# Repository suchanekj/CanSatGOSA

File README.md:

# About
CanSat code is software for autonomous exploration and landings of probe "CanSat" developed by Gymnazium Opatov Space Agency especially by Jakub Suchánek.

The whole code is using following subcodes:
* GroundStation - incoming datas of pressure, position, time and temperature
* Cansat (2.0) - used libraries - Code, Cirtuits...
* Final report (Detail information about the probe Cansat in LaTex article. Unfortunately only in Czech.)
* Pre launch report - English detail description of Cansat 2.0
* Analysis - our own atmospheric model running on data from CanSat
* After flight report - final description of the whole project

# Support
In case you need help with use of our program or support us, you can contact us on our public email dotazy@gosa.cz or on email of programming director suchanek989@seznam.cz

# Contributing

Contributions are welcome and encouraged.  You can contribute in many ways:

* Documentation updates and corrections.
* How-To guides - received help? Help others!
* Bug reporting & fixes.
* New feature ideas & suggestions.

# Requirements
* Hardware requirements: qbcan for matching ports or an AVR microcontroller with RFM69HW (will have to edit port specifications)
* Idealy used for original construction of CanSat: https://github.com/suchanekj/CanSatGOSA/tree/master/Schematics
* Also used for original construction of CanSat 2.0: https://github.com/suchanekj/CanSatGOSA/tree/master/CanSat2.0/Schematics 
* Software requirements: AVR chip programmmer

# Used code
* Uses the RFM69 Library from: Feix Rusu (2014), felix@lowpowerlab.com http://lowpowerlab.com/
* Inspired by qbcan library and hardware http://doc.open-cosmos.com/Qbcan_modular

# Open Source / Contributors
CanSat software that is **open source** and is available free of charge without warranty to all users.

Current contributors:
* Suchánek, Jakub (suchanekj)
* Novotný, Patrik  (PatriktheAstronomer)
* Vítek, Martin (MArtytraM99)
* Zeman, Jakub (Jakubzmn)
* Völfl, Lukáš (LukasVolfl)
# Versions:
* 1.0 Groundstation subcode created and README added 29/03/2018
* 1.1 CanSat subcode created and Model files completed 01/04/2018
* 1.2 Final report (LaTex article) created 03/04/2018
* 1.3 Final report (LaTex article) completed 12/04/2018
* 2.0 New contributers, Analysis, CanSat 2.0 3D printed parts and PLR.pdf (Pre-launch report) added 18/06/2018
* 2.1 Analysis part 2 completed, chamber software added 28/06/2018
* 2.2 After flight report added, Analysis repaired and added - project completely done 16/07/2018
 (**Thanks everyone for your support to our project!**)

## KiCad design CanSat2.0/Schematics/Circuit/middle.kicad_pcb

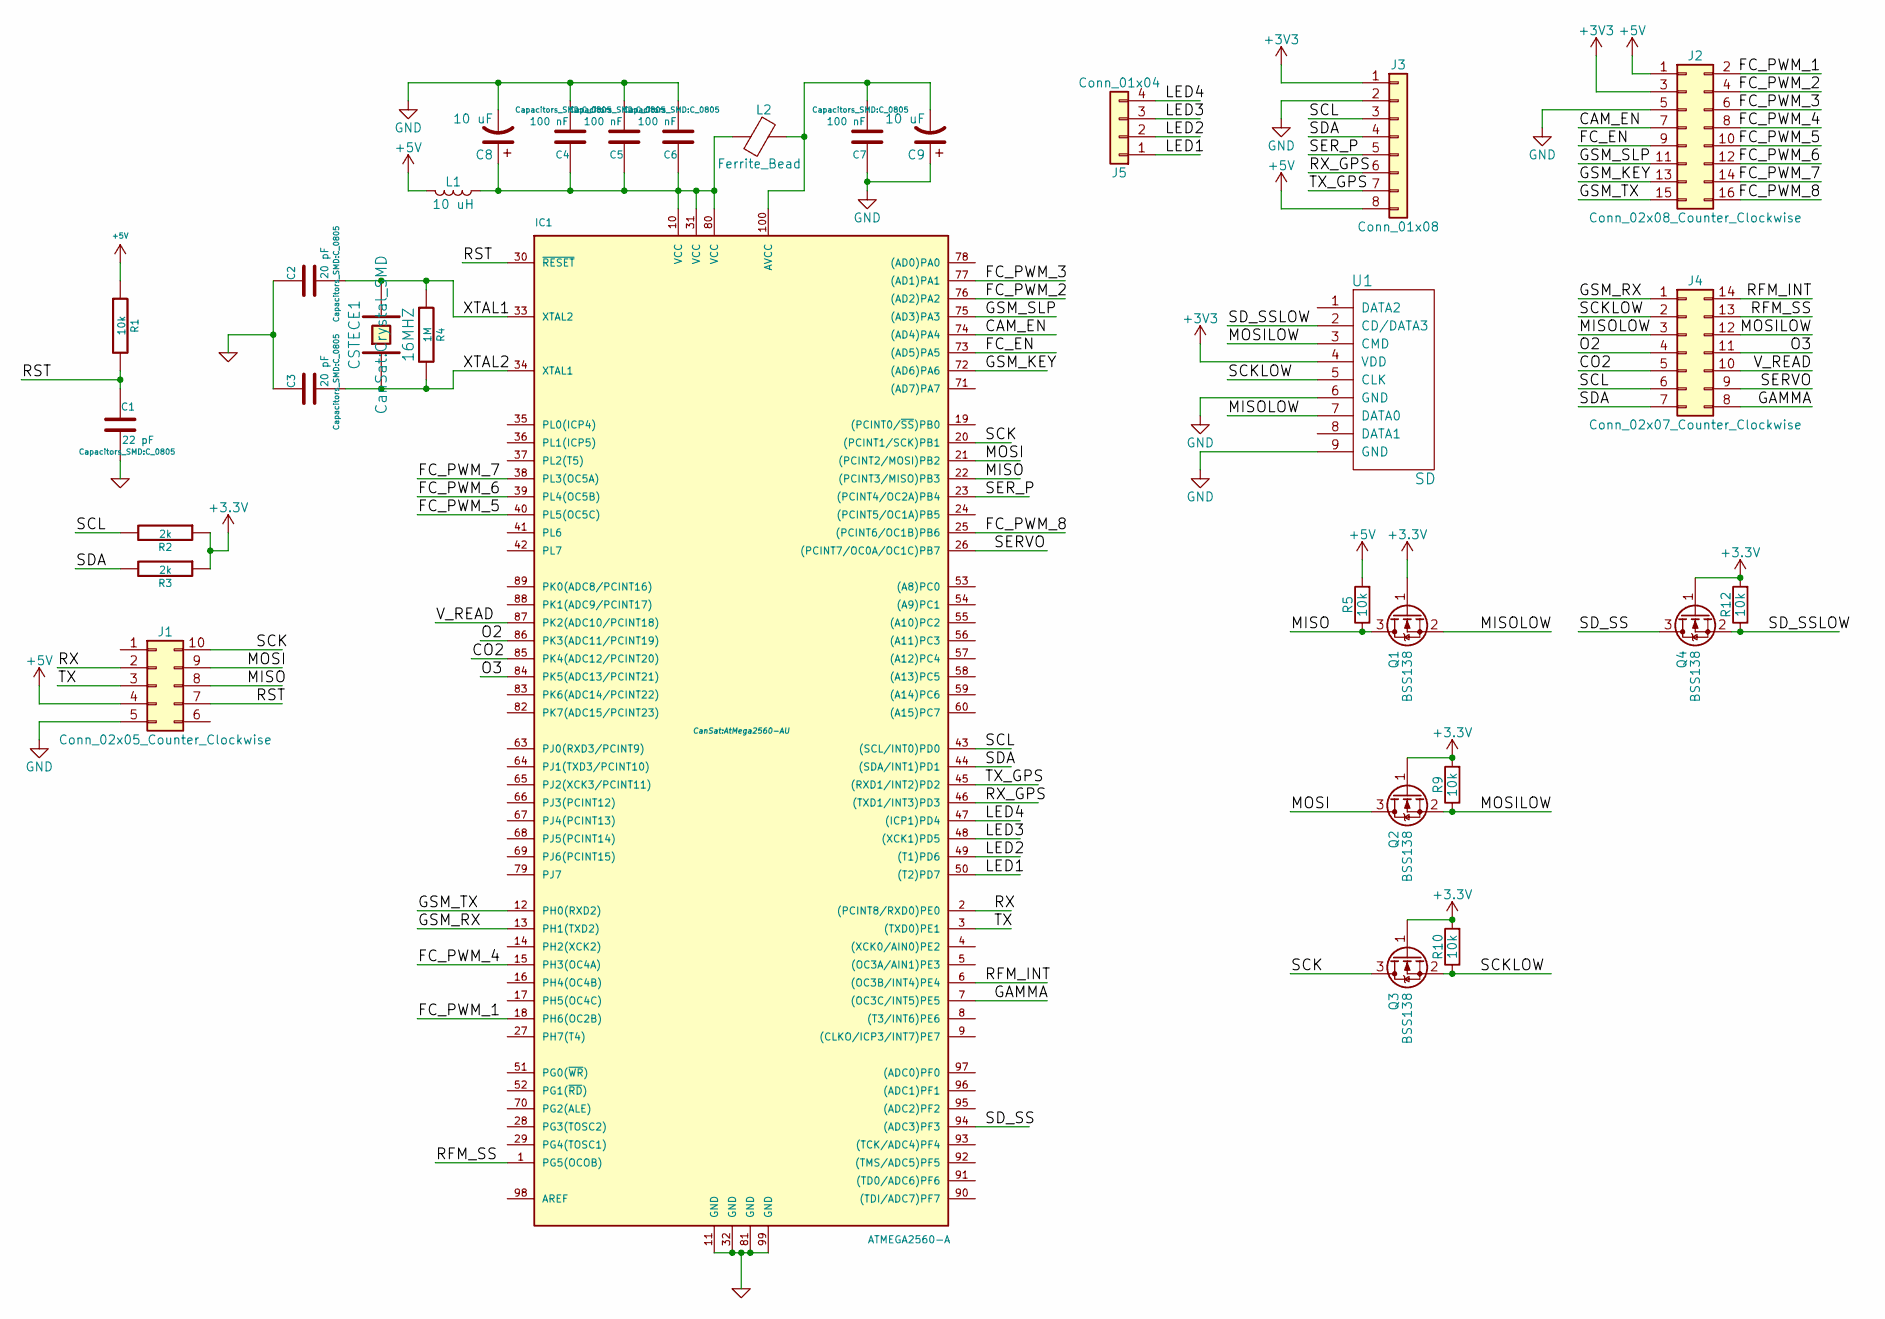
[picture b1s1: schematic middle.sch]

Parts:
C1: 22 pF; C_0805
C2, C3: 20 pF; C_0805
C4, C5, C6, C7: 100 nF; C_0805
C8, C9: 10 uF; CP_Tantalum_Case-B_EIA-3528-21_Reflow
CSTECE1: 16MHZ; Crystal_SMD
IC1: ATMEGA2560-A; AtMega2560-AU
J1: Conn_02x05_Counter_Clockwise; Pin_Header_Straight_2x05_Pitch1.27mm
J2: Conn_02x08_Counter_Clockwise; Pin_Header_Straight_2x08_Pitch1.27mm
J3: Conn_01x08; Pin_Header_Straight_1x08_Pitch1.27mm
J4: Conn_02x07_Counter_Clockwise; Pin_Header_Straight_2x07_Pitch1.27mm
J5: Conn_01x04; Pin_Header_Straight_1x04_Pitch1.27mm
L1: 10 uH; L_Taiyo-Yuden_NR-50xx
L2: Ferrite_Bead; L_0805
Q1, Q2, Q3, Q4: BSS138; SOT-23
R1, R5, R9, R10, R12: 10k; R_0805
R2, R3: 2k; R_0805
R4: 1M; R_0805
U1: SD

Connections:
+5V: J1.4, J2.1, J3.8, L1.2, R1.1, R5.2
/CAM_EN: IC1.74 ((AD4)PA4), J2.7
/CO2: IC1.85 (PK4(ADC12/PCINT20)), J4.5
/FC_EN: IC1.73 ((AD5)PA5), J2.9
/FC_PWM_1: IC1.18 (PH6(OC2B)), J2.2
/FC_PWM_2: IC1.76 ((AD2)PA2), J2.4
/FC_PWM_3: IC1.77 ((AD1)PA1), J2.6
/FC_PWM_4: IC1.15 (PH3(OC4A)), J2.8
/FC_PWM_5: IC1.40 (PL5(OC5C)), J2.10
/FC_PWM_6: IC1.39 (PL4(OC5B)), J2.12
/FC_PWM_7: IC1.38 (PL3(OC5A)), J2.14
/FC_PWM_8: IC1.25 ((PCINT6/OC1B)PB6), J2.16
/GAMMA: IC1.7 ((OC3C/INT5)PE5), J4.8
/GSM_KEY: IC1.72 ((AD6)PA6), J2.13
/GSM_RX: IC1.13 (PH1(TXD2)), J4.1
/GSM_SLP: IC1.75 ((AD3)PA3), J2.11
/GSM_TX: IC1.12 (PH0(RXD2)), J2.15
/LED1: IC1.50 ((T2)PD7), J5.1
/LED2: IC1.49 ((T1)PD6), J5.2
/LED3: IC1.48 ((XCK1)PD5), J5.3
/LED4: IC1.47 ((ICP1)PD4), J5.4
/MISO: IC1.22 ((PCINT3/MISO)PB3), J1.8, Q1.3 (D), R5.1
/MISOLOW: J4.3, Q1.2 (S), U1.7 (DATA0)
/MOSI: IC1.21 ((PCINT2/MOSI)PB2), J1.9, Q2.3 (D)
/MOSILOW: J4.12, Q2.2 (S), R9.1, U1.3 (CMD)
/O2: IC1.86 (PK3(ADC11/PCINT19)), J4.4
/O3: IC1.84 (PK5(ADC13/PCINT21)), J4.11
/RFM_INT: IC1.6 ((OC3B/INT4)PE4), J4.14
/RFM_SS: IC1.1 (PG5(OCOB)), J4.13
/RST: C1.1, IC1.30 (~RESET), J1.7, R1.2
/RX: IC1.2 ((PCINT8/RXD0)PE0), J1.2
/RX_GPS: IC1.46 ((TXD1/INT3)PD3), J3.6
/SCK: IC1.20 ((PCINT1/SCK)PB1), J1.10, Q3.3 (D)
/SCKLOW: J4.2, Q3.2 (S), R10.1, U1.5 (CLK)
/SCL: IC1.43 ((SCL/INT0)PD0), J3.3, J4.6, R2.2
/SDA: IC1.44 ((SDA/INT1)PD1), J3.4, J4.7, R3.2
/SD_SS: IC1.94 ((ADC3)PF3), Q4.3 (D)
/SD_SSLOW: Q4.2 (S), R12.1, U1.2 (CD/DATA3)
/SERVO: IC1.26 ((PCINT7/OC0A/OC1C)PB7), J4.9
/SER_P: IC1.23 ((PCINT4/OC2A)PB4), J3.5
/TX: IC1.3 ((TXD0)PE1), J1.3
/TX_GPS: IC1.45 ((RXD1/INT2)PD2), J3.7
/V_READ: IC1.87 (PK2(ADC10/PCINT18)), J4.10
/XTAL1: C2.2, CSTECE1.2, IC1.33 (XTAL2), R4.1
/XTAL2: C3.2, CSTECE1.1, IC1.34 (XTAL1), R4.2
GND: C1.2, C2.1, C3.1, C4.2, C5.2, C6.2, C7.1, C8.2, C9.1, IC1.11 (GND), IC1.32 (GND), IC1.81 (GND), IC1.99 (GND), J1.5, J2.5, J3.2, U1.6 (GND), U1.9 (GND)
unnamed: C4.1, C5.1, C6.1, C8.1, IC1.10 (VCC), IC1.31 (VCC), IC1.80 (VCC), L1.1, L2.2
unnamed: C7.2, C9.2, IC1.100 (AVCC), L2.1

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
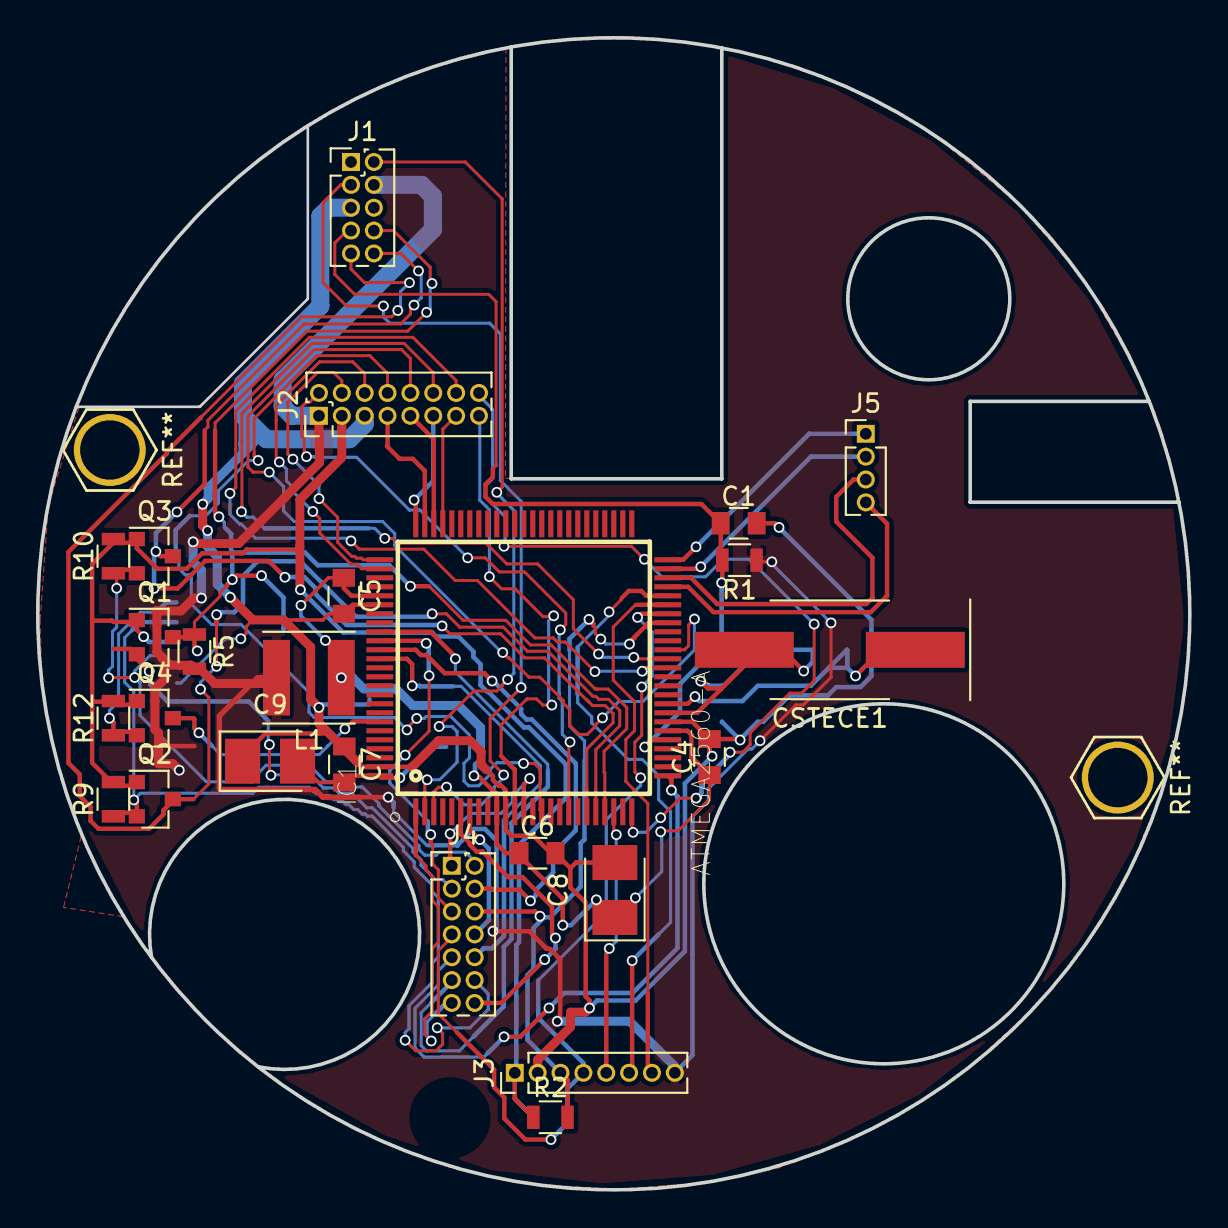
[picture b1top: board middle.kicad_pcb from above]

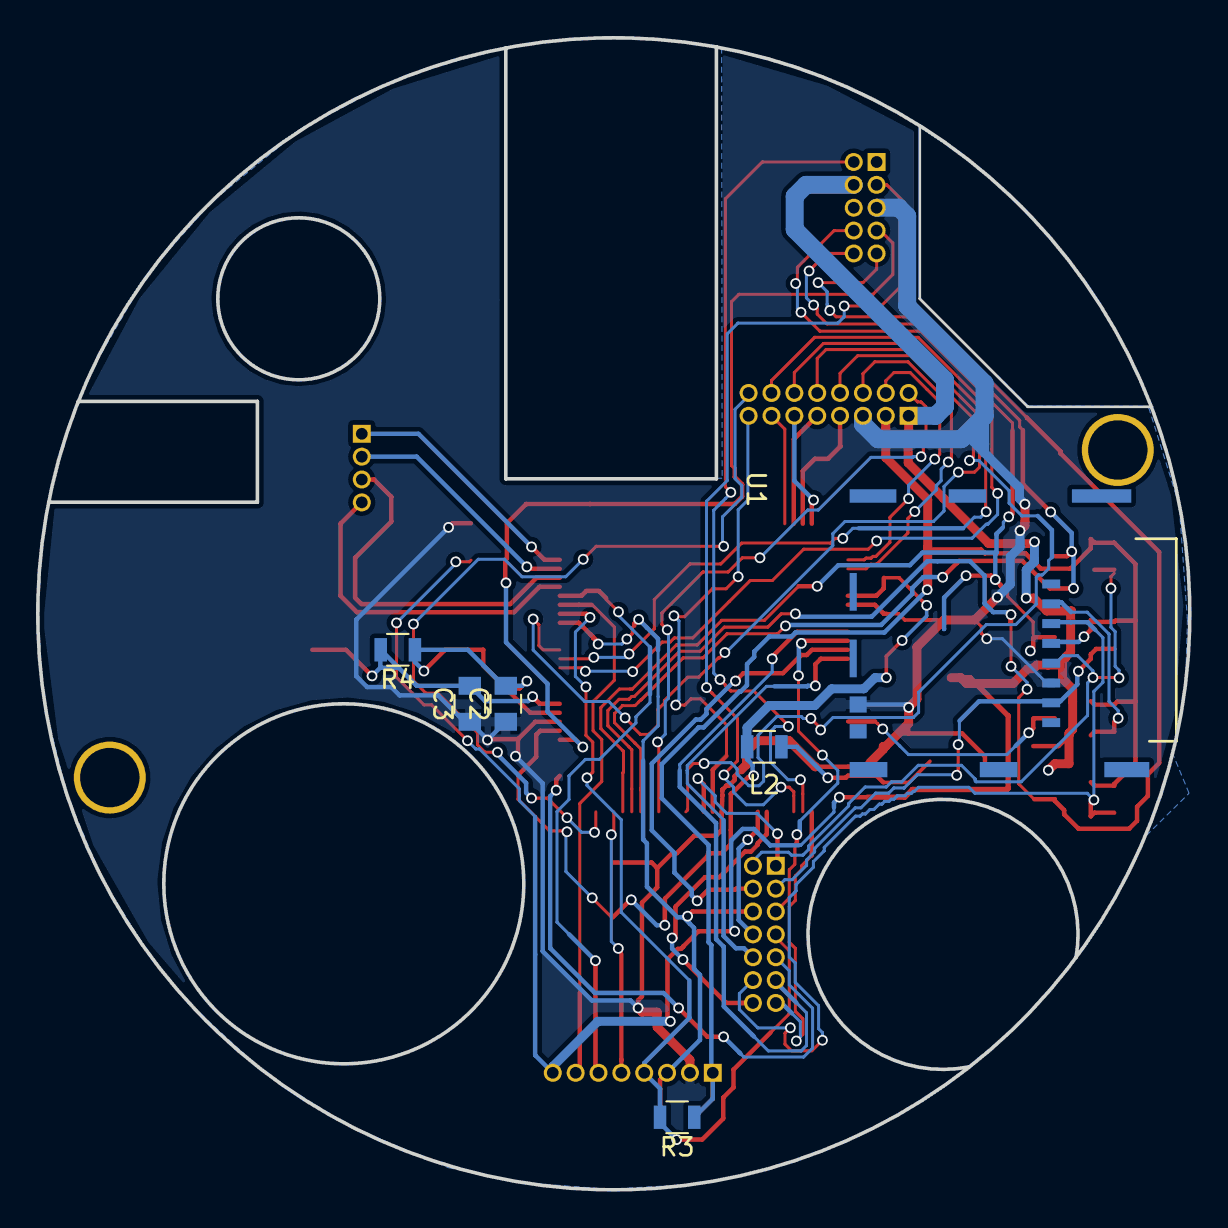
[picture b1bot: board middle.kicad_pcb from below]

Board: 2 copper layers, 64.0 x 64.0 mm, 31 parts (6 on the bottom side), 49 nets.

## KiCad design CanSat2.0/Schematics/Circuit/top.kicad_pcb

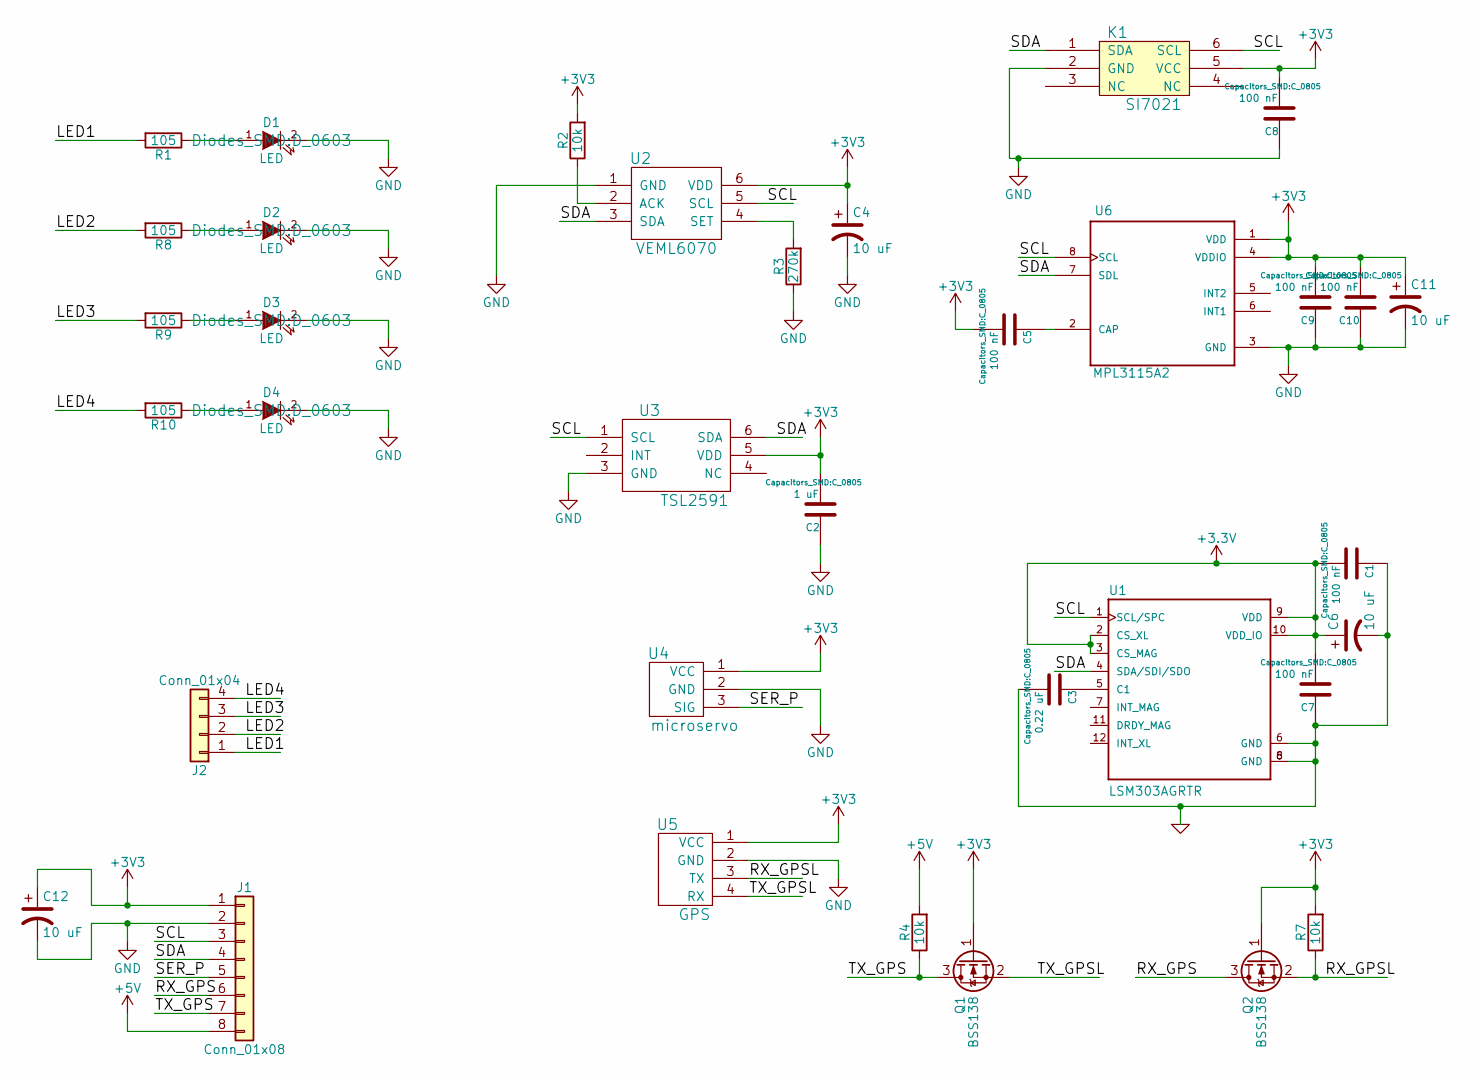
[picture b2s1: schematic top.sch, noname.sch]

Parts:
C1, C5, C7, C8, C9, C10: 100 nF; C_0805
C2: 1 uF; C_0805
C3: 0.22 uF; C_0805
C4, C6, C11, C12: 10 uF; CP_Tantalum_Case-T_EIA-3528-12_Reflow
D1, D2, D3, D4: LED; D_0603
J1: Conn_01x08; Pin_Header_Straight_1x08_Pitch1.27mm
J2: Conn_01x04; Pin_Header_Straight_1x04_Pitch1.27mm
K1: SI7021; DFN-6-1EP_3x3mm_Pitch0.95mm
Q1, Q2: BSS138; SOT-23
R1, R8, R9, R10: 105; R_0805
R2, R4, R7: 10k; R_0805
R3: 270k; R_0805
U1: LSM303AGRTR
U2: VEML6070; DFN-6-1EP_2x2mm_Pitch0.65mm
U3: TSL2591; AMS_LGA-10-1EP_2.7x4mm_Pitch0.6mm
U4: microservo
U5: GPS
U6: MPL3115A2; LGA-8_3x5mm_Pitch1.25mm

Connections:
+5V: J1.8, R4.2; also elsewhere on the board
/LED1: J2.1, R1.2
/LED2: J2.2, R8.2
/LED3: J2.3, R9.2
/LED4: J2.4, R10.2
/RX_GPS: J1.6, Q2.3 (D); also elsewhere on the board
/RX_GPSL: Q2.2 (S), R7.1, U5.3 (TX)
/SCL: J1.3, K1.6 (SCL), U1.1 (SCL/SPC), U2.5 (SCL), U3.1 (SCL), U6.8 (SCL)
/SDA: J1.4, K1.1 (SDA), U1.4 (SDA/SDI/SDO), U2.3 (SDA), U3.6 (SDA), U6.7 (SDL)
/SER_P: J1.5, U4.3 (SIG)
/TX_GPS: J1.7, Q1.3 (D), R4.1
/TX_GPSL: Q1.2 (S), U5.4 (RX); also elsewhere on the board
GND: C1.1, C2.1, C3.2, C4.2, C6.2, C7.1, C8.1, C9.1, C10.1, C11.2, C12.2, D1.2 (K), D2.2 (K), D3.2 (K), D4.2 (K), J1.2, K1.2 (GND), R3.1, U1.6 (GND), U1.8 (GND), U2.1 (GND), U3.3 (GND), U4.2 (GND), U5.2 (GND), U6.3 (GND)
unnamed: C3.1, U1.5 (C1)
unnamed: C5.1, U6.2 (CAP)
unnamed: D1.1 (A), R1.1
unnamed: D2.1 (A), R8.1
unnamed: D3.1 (A), R9.1
unnamed: D4.1 (A), R10.1
unnamed: R2.1, U2.2 (ACK)
unnamed: R3.2, U2.4 (SET)

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
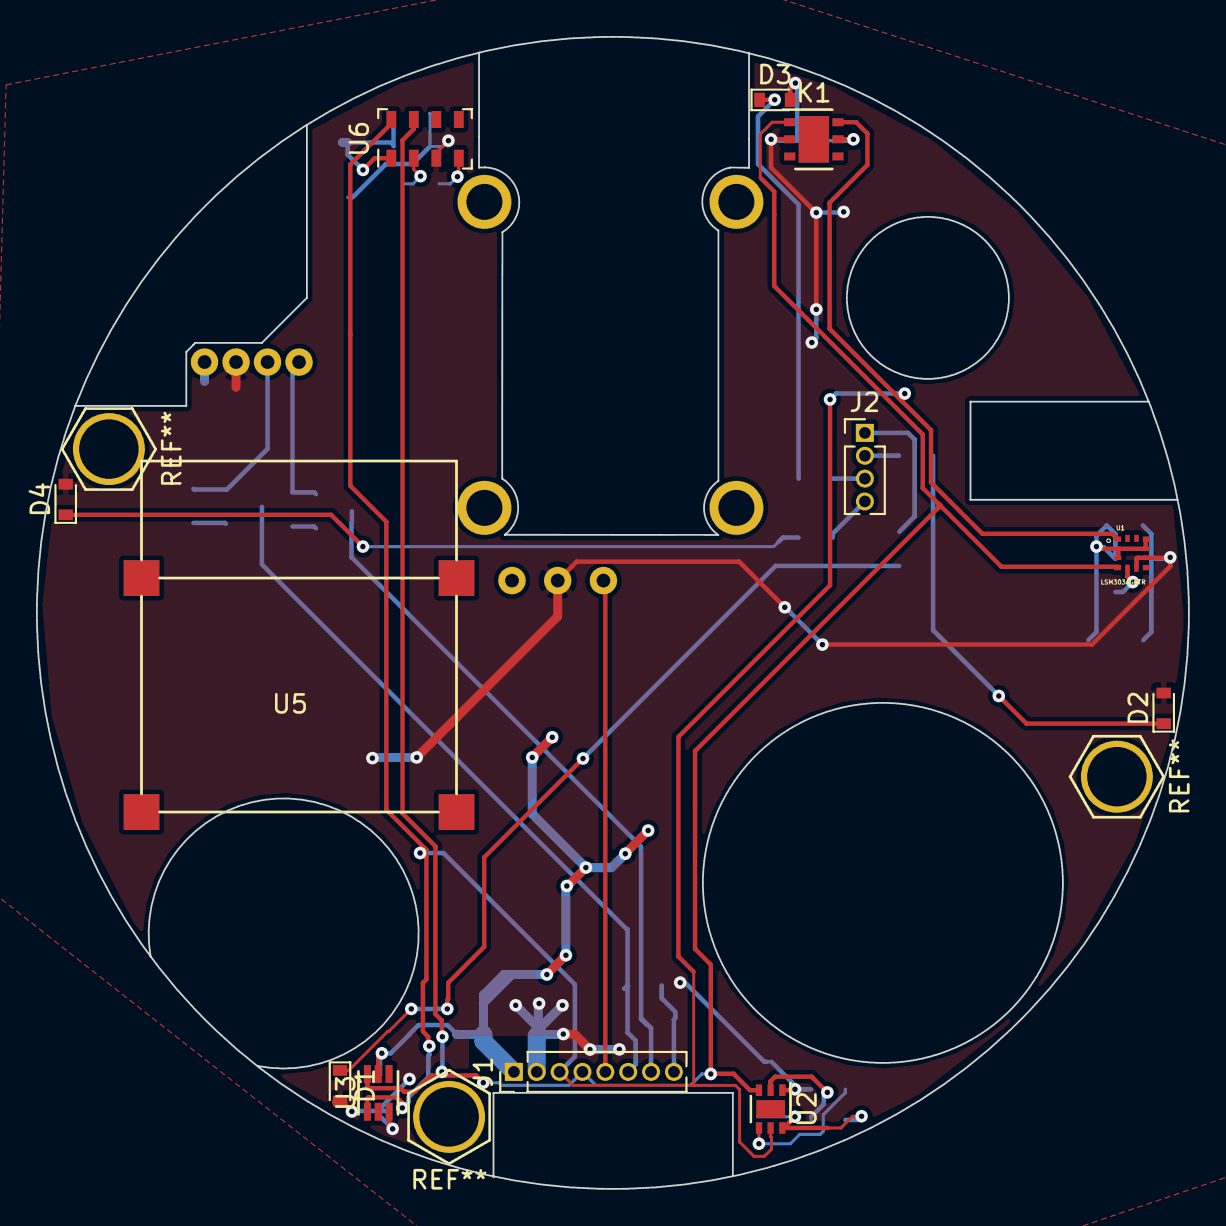
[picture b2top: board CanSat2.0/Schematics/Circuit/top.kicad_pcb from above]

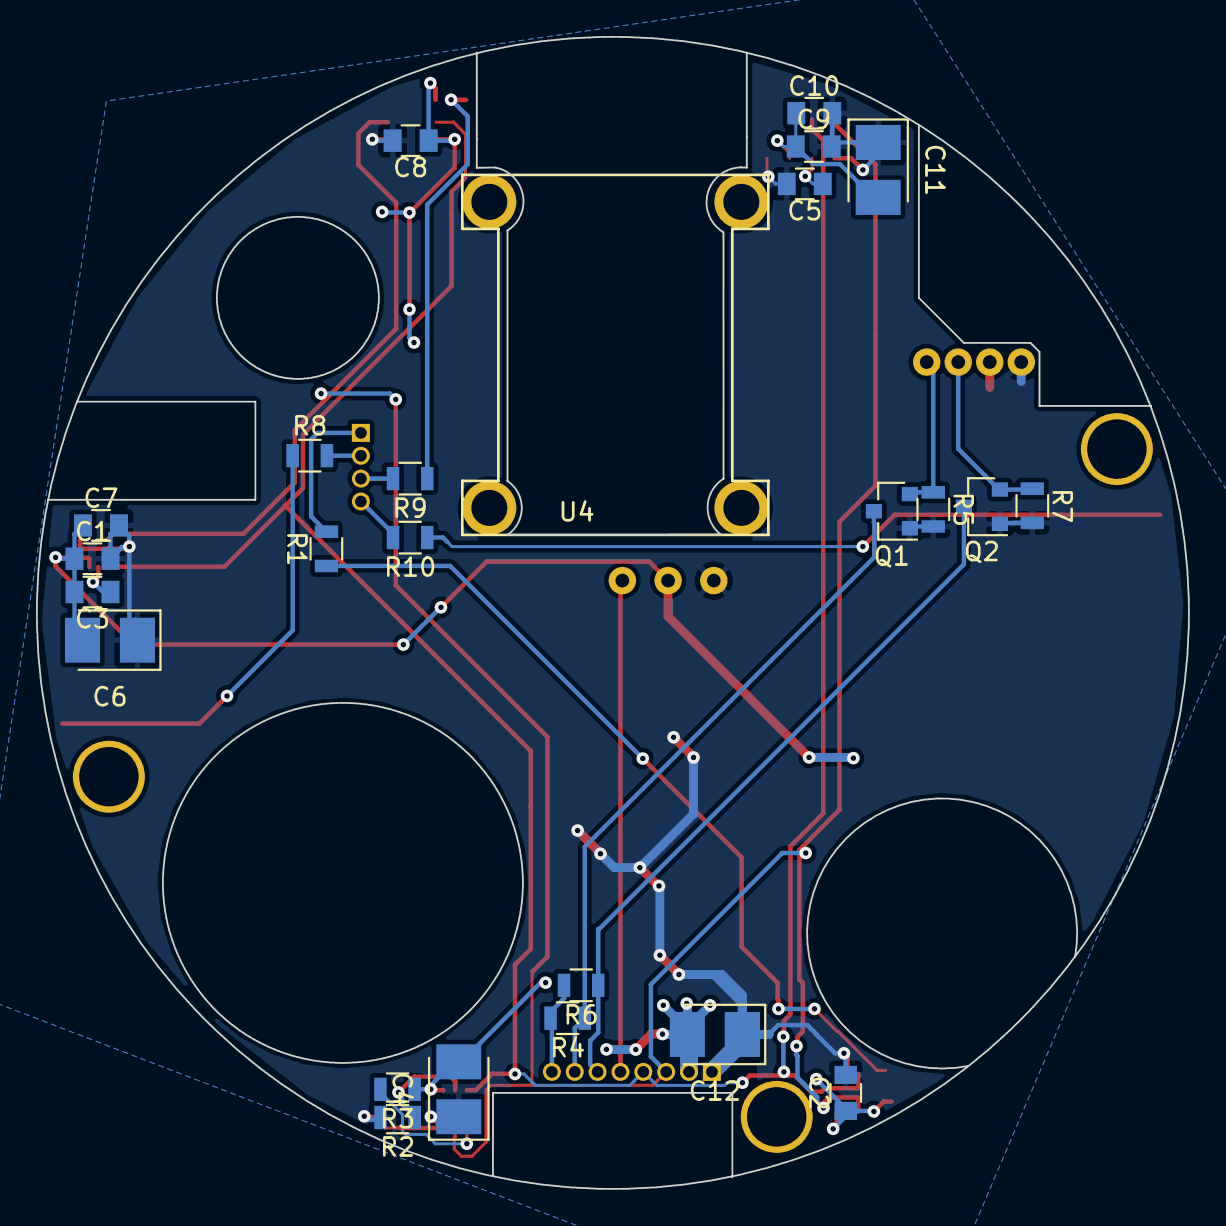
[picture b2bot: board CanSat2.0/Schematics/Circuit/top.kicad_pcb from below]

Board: 2 copper layers, 64.0 x 64.0 mm, 37 parts (25 on the bottom side), 22 nets.

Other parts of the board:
R5, R6: 10k; R_0805

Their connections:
+5V: R6.2; also elsewhere on the board
/RX_GPS: R6.1; also elsewhere on the board
/TX_GPSL: R5.1; also elsewhere on the board

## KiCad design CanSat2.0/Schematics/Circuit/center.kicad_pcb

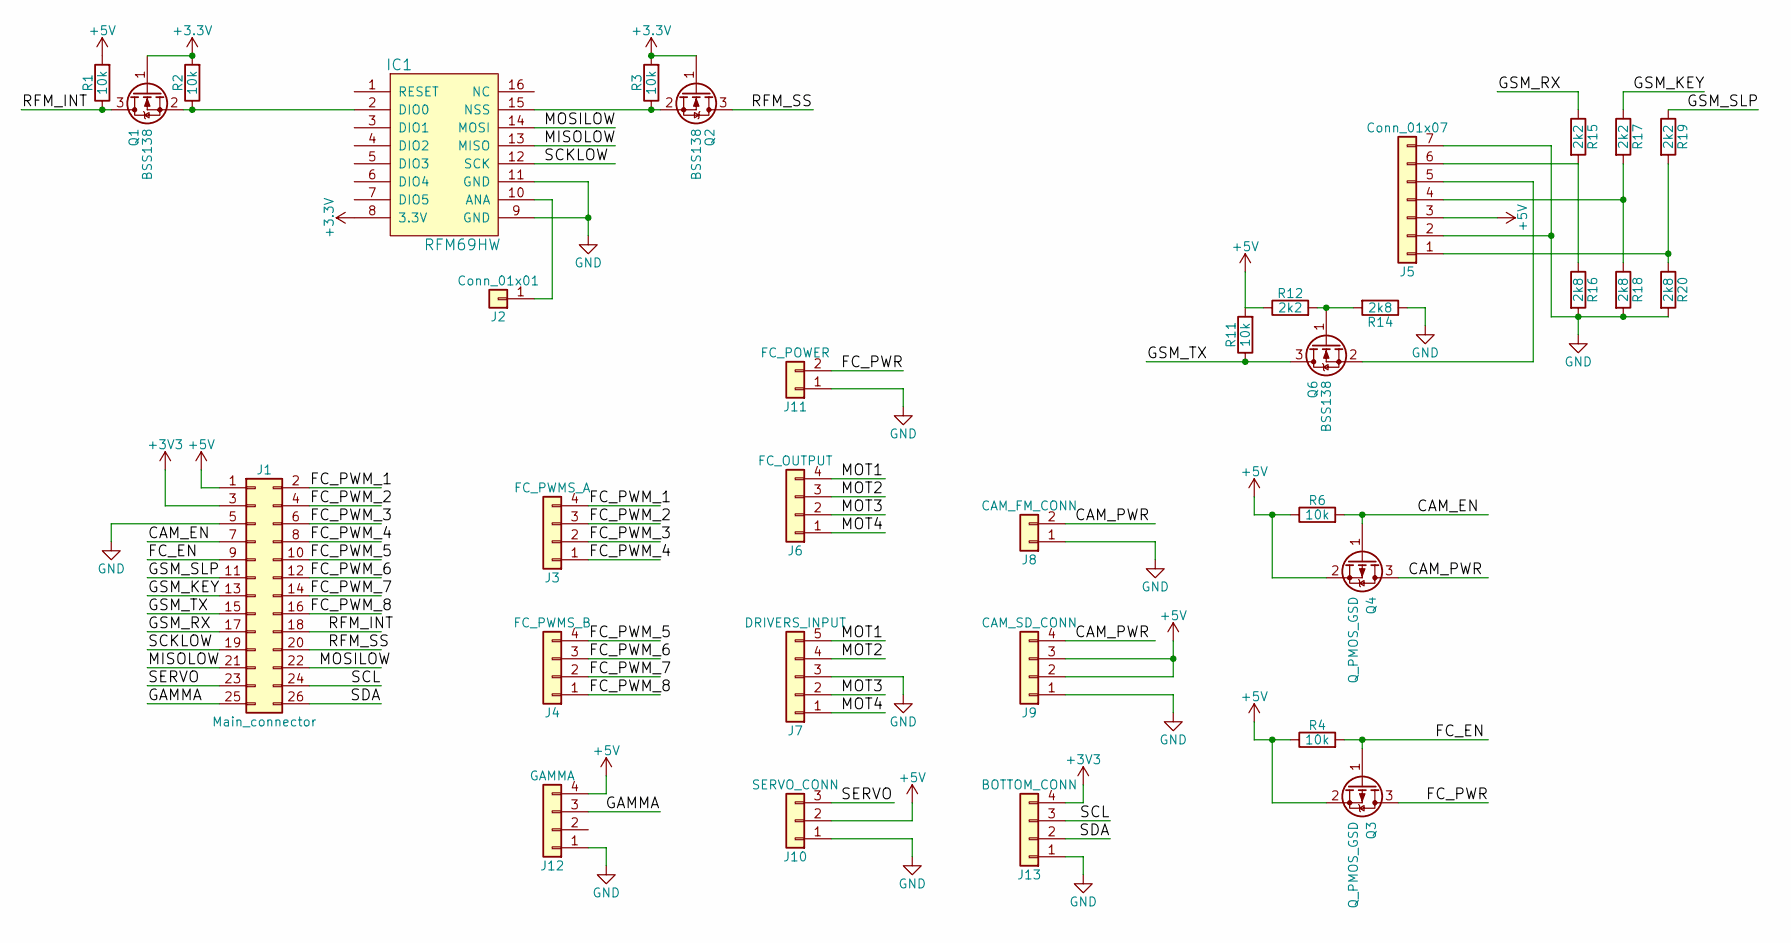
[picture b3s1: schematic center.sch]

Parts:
IC1: RFM69HW
J1: Main_connector; Pin_Header_Angled_2x13_Pitch1.27mm
J2: Conn_01x01; Pin_Header_Straight_1x01_Pitch2.54mm
J3: FC_PWMS_A; Pin_Header_Straight_1x04_Pitch1.27mm
J4: FC_PWMS_B; Pin_Header_Straight_1x04_Pitch1.27mm
J5: Conn_01x07; Pin_Header_Straight_1x07_Pitch2.54mm
J6: FC_OUTPUT; Pin_Header_Straight_1x04_Pitch2.54mm
J7: DRIVERS_INPUT; Pin_Header_Straight_1x05_Pitch1.27mm
J8: CAM_FM_CONN; Pin_Header_Straight_1x02_Pitch2.54mm
J9: CAM_SD_CONN; Pin_Header_Straight_1x04_Pitch2.54mm
J10: SERVO_CONN; Pin_Header_Straight_1x03_Pitch2.54mm
J11: FC_POWER; Pin_Header_Straight_1x02_Pitch2.54mm
J12: GAMMA; Pin_Header_Straight_1x04_Pitch2.54mm
J13: BOTTOM_CONN; Pin_Header_Angled_1x04_Pitch2.54mm
Q1, Q2, Q6: BSS138; SOT-23
Q3, Q4: Q_PMOS_GSD; SOT-23
R1, R2, R3, R4, R6, R11: 10k; R_0805
R12, R15, R17, R19: 2k2; R_0805
R14, R16, R18, R20: 2k8; R_0805

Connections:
+5V: J1.1, J5.3, J9.2, J9.3, J10.2, J12.4, Q3.2 (S), Q4.2 (S), R1.2, R4.1, R6.1, R11.2, R12.1
/CAM_EN: J1.7, Q4.1 (G), R6.2
/CAM_PWR: J8.2, J9.4, Q4.3 (D)
/FC_EN: J1.9, Q3.1 (G), R4.2
/FC_PWM_1: J1.2, J3.4
/FC_PWM_2: J1.4, J3.3
/FC_PWM_3: J1.6, J3.2
/FC_PWM_4: J1.8, J3.1
/FC_PWM_5: J1.10, J4.4
/FC_PWM_6: J1.12, J4.3
/FC_PWM_7: J1.14, J4.2
/FC_PWM_8: J1.16, J4.1
/FC_PWR: J11.2, Q3.3 (D)
/GAMMA: J1.25, J12.3
/GSM_KEY: J1.13, R17.1
/GSM_RX: J1.17, R15.1
/GSM_SLP: J1.11, R19.1
/GSM_TX: J1.15, Q6.3 (D), R11.1
/MISOLOW: IC1.13 (MISO), J1.21
/MOSILOW: IC1.14 (MOSI), J1.22
/MOT1: J6.4, J7.5
/MOT2: J6.3, J7.4
/MOT3: J6.2, J7.2
/MOT4: J6.1, J7.1
/RFM_INT: J1.18, Q1.3 (D), R1.1
/RFM_SS: J1.20, Q2.3 (D)
/SCKLOW: IC1.12 (SCK), J1.19
/SCL: J1.24, J13.3
/SDA: J1.26, J13.2
/SERVO: J1.23, J10.3
GND: IC1.9 (GND), IC1.11 (GND), J1.5, J5.2, J5.7, J7.3, J8.1, J9.1, J10.1, J11.1, J12.1, J13.1, R14.1, R16.2, R18.2, R20.2
unnamed: IC1.2 (DIO0), Q1.2 (S), R2.1
unnamed: IC1.10 (ANA), J2.1
unnamed: IC1.15 (NSS), Q2.2 (S), R3.1
unnamed: J5.1, R19.2, R20.1
unnamed: J5.4, R17.2, R18.1
unnamed: J5.5, Q6.2 (S)
unnamed: J5.6, R15.2, R16.1
unnamed: Q6.1 (G), R12.2, R14.2

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
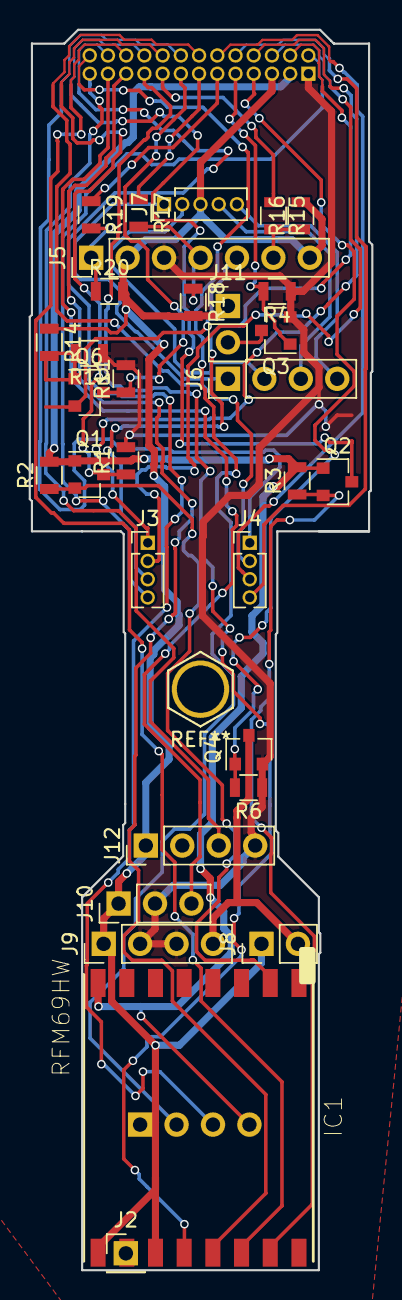
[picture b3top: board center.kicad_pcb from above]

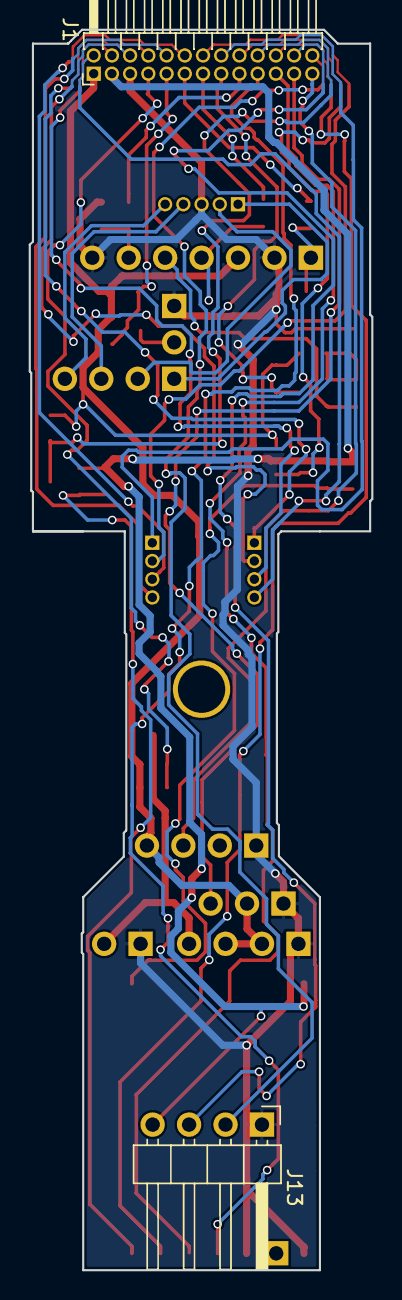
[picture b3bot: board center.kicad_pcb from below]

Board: 2 copper layers, 23.9 x 86.5 mm, 33 parts (2 on the bottom side), 40 nets.

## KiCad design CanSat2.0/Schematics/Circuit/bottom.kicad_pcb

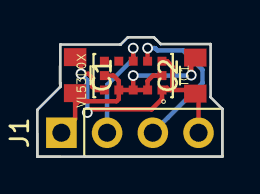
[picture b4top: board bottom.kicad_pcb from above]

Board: 2 copper layers, 10.3 x 6.6 mm, 4 parts (0 on the bottom side), 4 nets.

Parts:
C1: 100nF; C_0805
C2: 4.7uF; C_0805
IC1: VL53L0X; XDCR_VL53L0CXV0DH%2f1
J1: CENTER_CONN; Pin_Header_Straight_1x04_Pitch2.54mm

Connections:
+3V3: C1.1, C2.1, IC1.1, IC1.1.1, IC1.5, IC1.11, J1.4
/SCL: IC1.10, J1.3
/SDA: IC1.9, J1.2
GND: C1.2, C2.2, IC1.2, IC1.3, IC1.4, IC1.6, IC1.12, J1.1

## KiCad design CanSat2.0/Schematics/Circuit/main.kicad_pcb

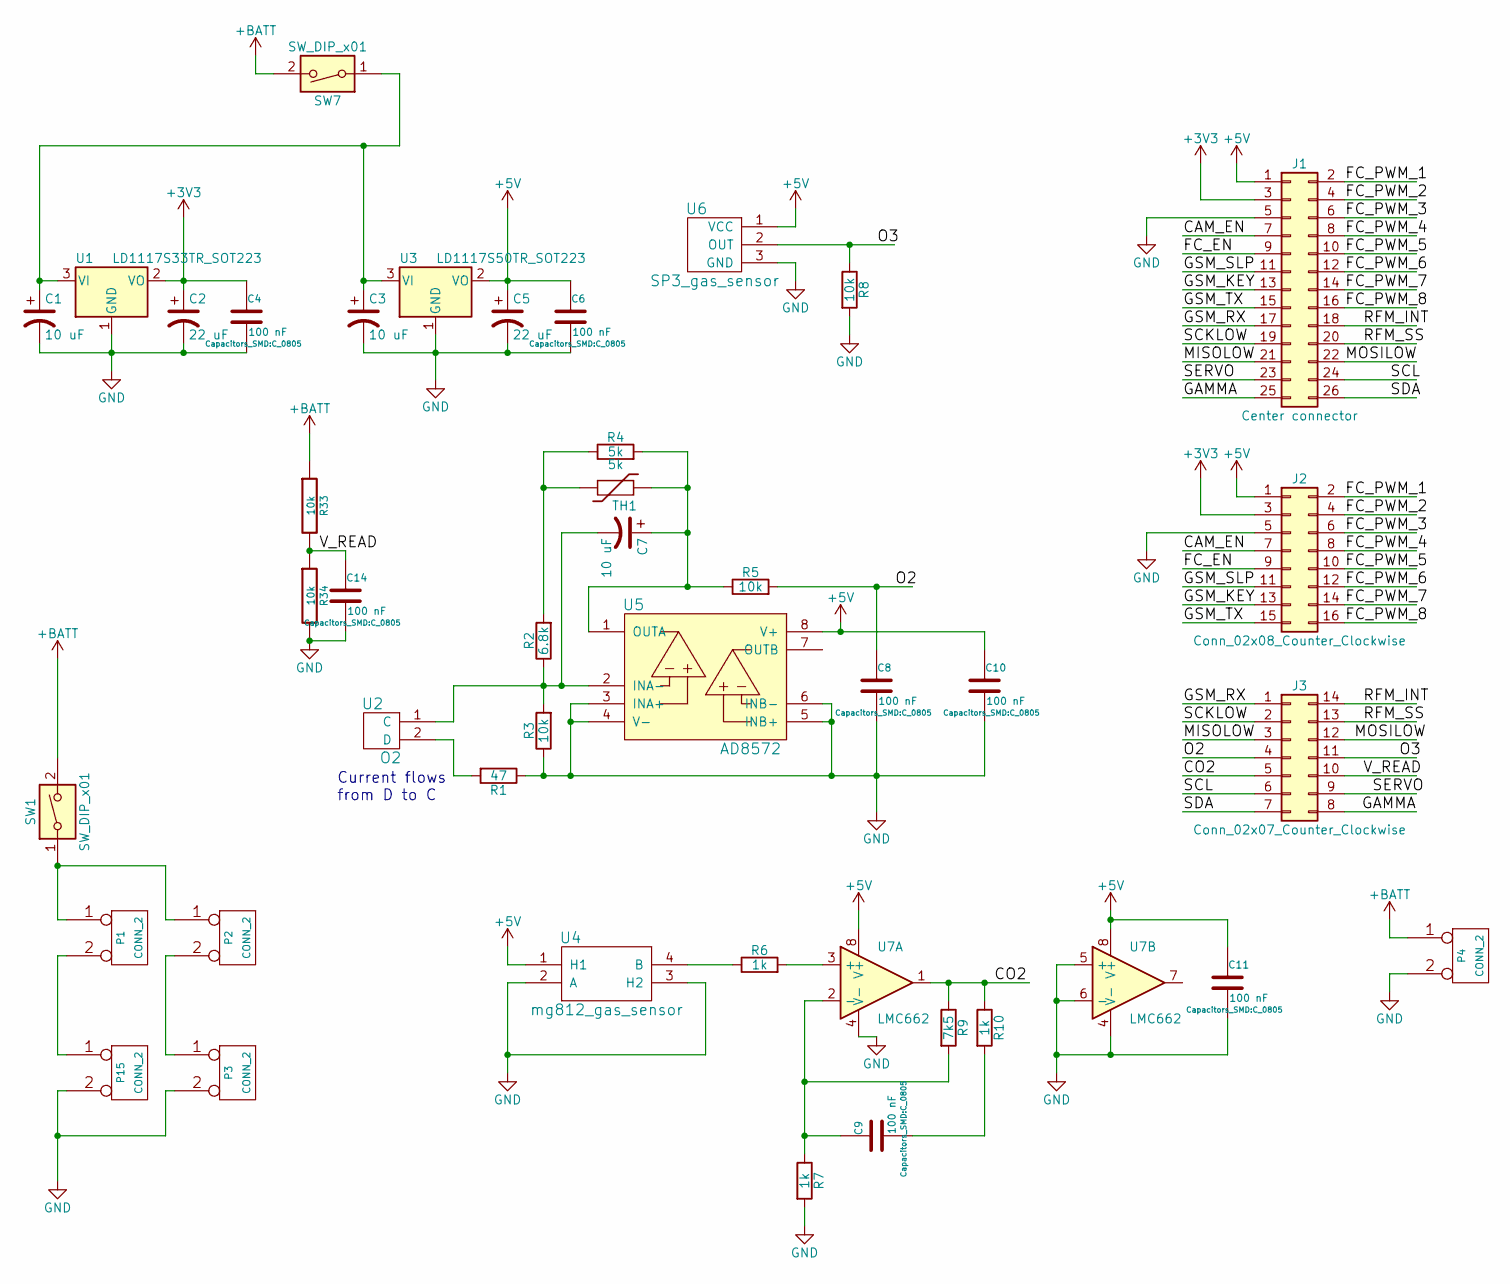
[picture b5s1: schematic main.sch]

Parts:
C1, C3, C7: 10 uF; CP_Tantalum_Case-T_EIA-3528-12_Reflow
C2, C5: 22 uF; CP_Tantalum_Case-T_EIA-3528-12_Reflow
C4, C6, C8, C9, C10, C11, C14: 100 nF; C_0805
J1: Center connector; Pin_Header_Straight_2x13_Pitch1.27mm_SMD
J2: Conn_02x08_Counter_Clockwise; Pin_Header_Straight_2x08_Pitch1.27mm
J3: Conn_02x07_Counter_Clockwise; Pin_Header_Straight_2x07_Pitch1.27mm
P1, P2, P3, P15: CONN_2; TX30
P4: CONN_2; TX30_vertical
R1: 47; R_0805
R2: 6.8k; R_0805
R3, R5, R8, R33, R34: 10k; R_0805
R4: 5k; R_0805
R6, R7, R10: 1k; R_0805
R9: 7k5; R_0805
SW1: SW_DIP_x01; TX30_vertical
SW7: SW_DIP_x01; Switch
TH1: 5k; R_0805
U1: LD1117S33TR_SOT223; SOT-223-3_TabPin2
U2: O2
U3: LD1117S50TR_SOT223; SOT-223-3_TabPin2
U4: mg812_gas_sensor; mg812
U5: AD8572; SO-8_5.3x6.2mm_Pitch1.27mm
U6: SP3_gas_sensor; O3
U7: LMC662; SOIC-8_3.9x4.9mm_Pitch1.27mm

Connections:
+3V3: C2.1, C4.1, J1.3, J2.3, U1.2 (VO)
+5V: C5.1, C6.1, C10.1, C11.1, J1.1, J2.1, U3.2 (VO), U4.1 (H1), U5.8 (V+), U6.1 (VCC), U7.8 (V+)
+BATT: P4.1, R33.1, SW1.2, SW7.2
/CAM_EN: J1.7, J2.7
/CO2: J3.5, R9.1, R10.1, U7.1
/FC_EN: J1.9, J2.9
/FC_PWM_1: J1.2, J2.2
/FC_PWM_2: J1.4, J2.4
/FC_PWM_3: J1.6, J2.6
/FC_PWM_4: J1.8, J2.8
/FC_PWM_5: J1.10, J2.10
/FC_PWM_6: J1.12, J2.12
/FC_PWM_7: J1.14, J2.14
/FC_PWM_8: J1.16, J2.16
/GAMMA: J1.25, J3.8
/GSM_KEY: J1.13, J2.13
/GSM_RX: J1.17, J3.1
/GSM_SLP: J1.11, J2.11
/GSM_TX: J1.15, J2.15
/MISOLOW: J1.21, J3.3
/MOSILOW: J1.22, J3.12
/O2: C8.1, J3.4, R5.2
/O3: J3.11, R8.1, U6.2 (OUT)
/RFM_INT: J1.18, J3.14
/RFM_SS: J1.20, J3.13
/SCKLOW: J1.19, J3.2
/SCL: J1.24, J3.6
/SDA: J1.26, J3.7
/SERVO: J1.23, J3.9
/V_READ: C14.1, J3.10, R33.2, R34.1
GND: C1.2, C2.2, C3.2, C4.2, C5.2, C6.2, C8.2, C10.2, C11.2, C14.2, J1.5, J2.5, P3.2 (PM), P4.2 (PM), P15.2 (PM), R1.1, R3.1, R7.2, R8.2, R34.2, U1.1 (GND), U3.1 (GND), U4.2 (A), U4.3 (H2), U5.3 (INA+), U5.4 (V-), U5.5 (INB+), U5.6 (INB-), U6.3 (GND), U7.4 (V-), U7.5 (+), U7.6 (-)
unnamed: C1.1, C3.1, SW7.1, U1.3 (VI), U3.3 (VI)
unnamed: C7.1, R4.2, R5.1, TH1.1, U5.1 (OUTA)
unnamed: C7.2, R2.1, R3.2, U2.1 (C), U5.2 (INA-)
unnamed: C9.1, R7.1, R9.2, U7.2 (-)
unnamed: C9.2, R10.2
unnamed: P1.1, P2.1, SW1.1
unnamed: P1.2 (PM), P15.1
unnamed: P2.2 (PM), P3.1
unnamed: R1.2, U2.2 (D)
unnamed: R2.2, R4.1, TH1.2
unnamed: R6.1, U4.4 (B)
unnamed: R6.2, U7.3 (+)

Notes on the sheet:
Current flows from D to C
